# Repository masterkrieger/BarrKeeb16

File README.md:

# BarrKeeb16
 This is a 16 key macro keypad with a rotary encoder, OLED display and under-glow RGB. BarrKeeb16 is running KMK firmware on the Seeed XIAO RP2040.

# Parts
1. BarrKeeb16 custom PCB. [JLCPCB](https://jlcpcb.com/)
2. Seeed XIAO RP2040. [Digikey](https://www.digikey.com/en/products/detail/seeed-technology-co-ltd/102010428/14672129?s=N4IgTCBcDaIB4EsCGB7ABAJwA5gAwBZcQBdAXyA) ― [SeeedStudio](https://www.seeedstudio.com/XIAO-RP2040-v1-0-p-5026.html)
3. 16 × Diodes (SOD-123) [Digikey](https://www.digikey.ca/en/products/detail/smc-diode-solutions/1N4148W/6022450)
4. 16 × Cherry MX style switches. [Digikey](https://www.digikey.ca/en/products/detail/adafruit-industries-llc/4952/14113453) ― [Adafruit](https://www.adafruit.com/product/4952)
5. 16 × DSA style keycaps. [Digikey](https://www.digikey.ca/en/products/detail/adafruit-industries-llc/4998/14552195) ― [Adafruit](https://www.adafruit.com/product/4998)
6. 1 × Encoder (PEC11R). [Digikey](https://www.digikey.ca/en/products/detail/bourns-inc/PEC11R-4215F-S0024/4499665) ― [Adafruit](https://www.adafruit.com/product/377)
7. 4 × Neopixel 5050 (SK6812 or WS2812 _ 5mm × 5mm) [Digikey](https://www.digikey.ca/en/products/detail/adafruit-industries-llc/1655/5154679) ― [Adafruit](https://www.adafruit.com/product/1655)
8. 4 × 0.1 µF Capacitors 0603 (1608 Metric). [Digikey](https://www.digikey.ca/en/products/detail/samsung-electro-mechanics/CL10B104KB8NNNL/3894274)
9. 1 × Level shifter SOT-23-5. [Digikey](https://www.digikey.ca/en/products/detail/texas-instruments/74AHCT1G125DBVTG4/1687957)
10. 1 × PCF8574 IO Expander. [Digikey](https://www.digikey.ca/en/products/detail/nxp-usa-inc/PCF8574T-3-512/735690)
10. 1 × 10 kOhms Resistor 0805 (2012 Metric). [Digikey](https://www.digikey.ca/en/products/detail/stackpole-electronics-inc/RMCF0805JG10K0/1757769)
10. 1 × 4.7 kOhms Resistor 0805 (2012 Metric). [Digikey](https://www.digikey.ca/en/products/detail/stackpole-electronics-inc/RMCF0805JT4K70/1757774)
11. 5 × Screws (M2 × 2.5mm)
12. 4 × Rubber Bumper Feet. [Adafruit](https://www.adafruit.com/product/550)

# OLED Image
 If you want to replace the BarrKeeb16_screenlogo bitmap, create any black and white 128x64 pixel image and rename as 'BarrKeeb16_screenlogo.bmp' or 'BarrKeeb16_screenlogo_inverted.bmp' or modify the image filename in [display_logo.py](https://github.com/masterkrieger/BarrKeeb16/blob/main/Firmware/display_logo.py).

## TODO:
- Update STL models with new OLED position (v1.2).
- Update FIRMWARE with new RP2040 and IO Expander pinouts (v1.2).

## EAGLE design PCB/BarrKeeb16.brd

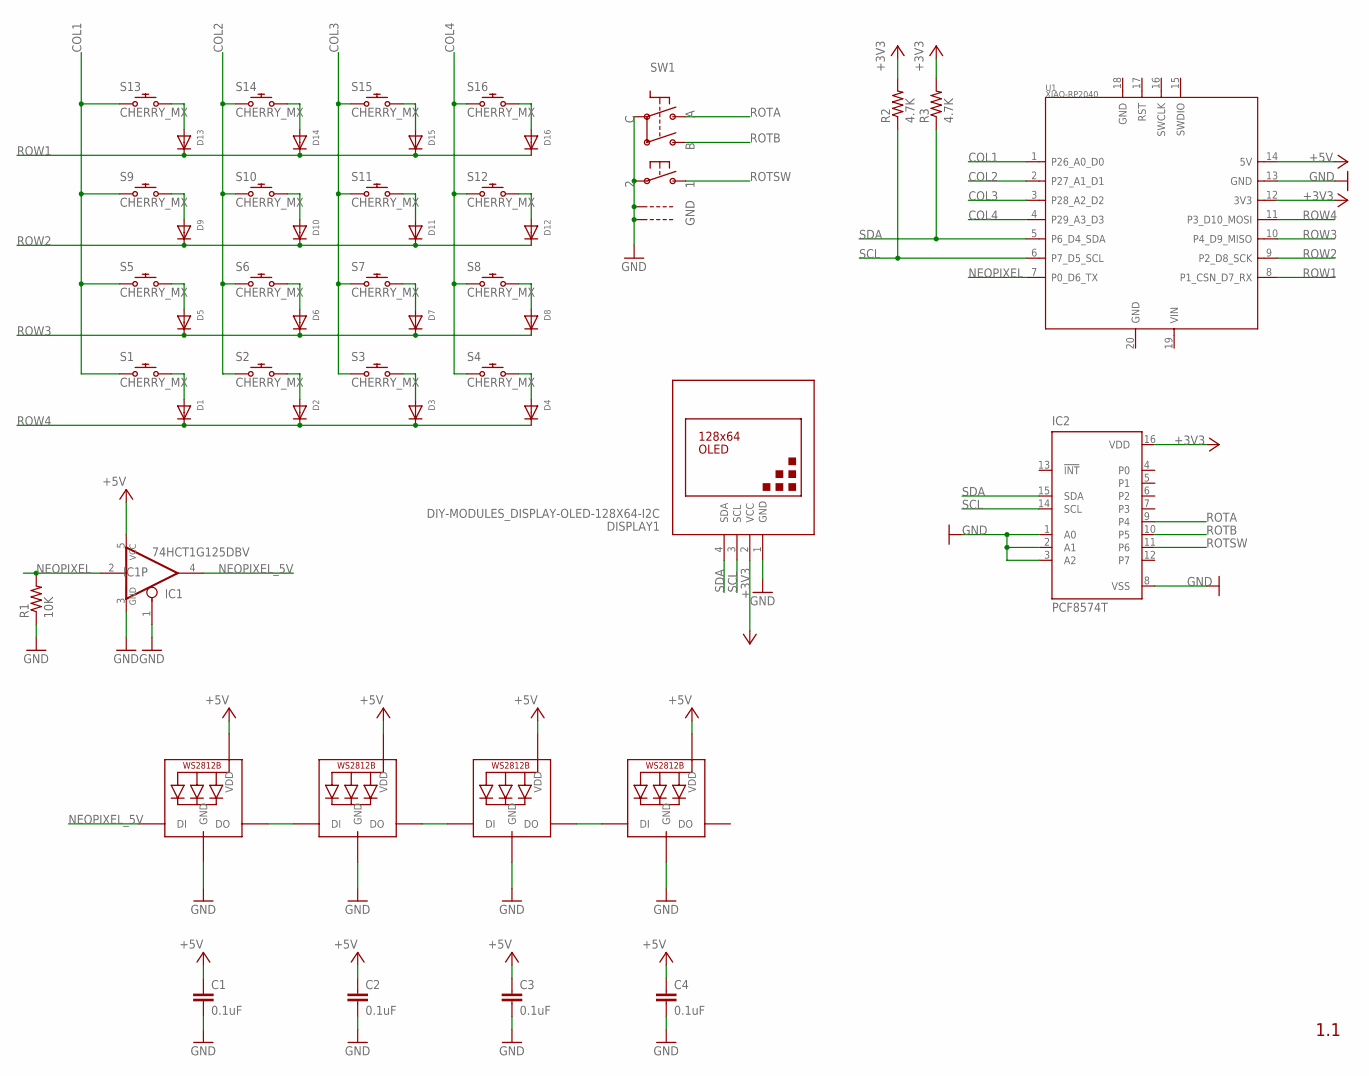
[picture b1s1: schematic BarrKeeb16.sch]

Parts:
C1, C2, C3, C4: 0.1uF; 0603
D1, D2, D3, D4, D5, D6, D7, D8, D9, D10, D11, D12, D13, D14, D15, D16: MICROBUILDER_DIODESOD-123; MICROBUILDER_SOD-123
DISPLAY1: DIY-MODULES_DISPLAY-OLED-128X64-I2C
IC1: 74HCT1G125DBV; SOT23-5
IC2: PCF8574T; SO16W
LED1, LED2, LED3, LED4: WS2812B5050; WS2812B
R1: 10K; R0805
R2, R3: 4.7K; R0805
S1, S2, S3, S4, S5, S6, S7, S8, S9, S10, S11, S12, S13, S14, S15, S16: CHERRY_MX
SW1: ADAFRUIT_ELECTROMECH_ENCODER_PLUS_SWITCH_BOURNS_P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; ADAFRUIT_ELECTROMECH_PEC11+SWITCH
U1: XIAO-RP2040; XIAO-SAMD21/RP2040-MODULE14P-2.54-21X17.8MM

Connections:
+3V3: DISPLAY1.2 (VCC), IC2.16 (VDD), R2.2, R3.2, U1.12 (3V3)
+5V: C1.1, C2.1, C3.1, C4.1, IC1.5 (VCC), LED1.1-VDD (VDD), LED2.1-VDD (VDD), LED3.1-VDD (VDD), LED4.1-VDD (VDD), U1.14 (5V)
COL1: S1.S1 (1), S5.S1 (1), S9.S1 (1), S13.S1 (1), U1.1 (P26_A0_D0)
COL2: S2.S1 (1), S6.S1 (1), S10.S1 (1), S14.S1 (1), U1.2 (P27_A1_D1)
COL3: S3.S1 (1), S7.S1 (1), S11.S1 (1), S15.S1 (1), U1.3 (P28_A2_D2)
COL4: S4.S1 (1), S8.S1 (1), S12.S1 (1), S16.S1 (1), U1.4 (P29_A3_D3)
GND: C1.2, C2.2, C3.2, C4.2, DISPLAY1.1 (GND), IC1.1 (OE), IC1.3 (GND), IC2.1 (A0), IC2.2 (A1), IC2.3 (A2), IC2.8 (VSS), LED1.3-GND (GND), LED2.3-GND (GND), LED3.3-GND (GND), LED4.3-GND (GND), R1.1, SW1.P$2, SW1.P$C, SW1.P$GND1, SW1.P$GND2, U1.13 (GND)
unnamed: D13.A, S13.S2 (2)
unnamed: D14.A, S14.S2 (2)
unnamed: LED1.2-DOUT (DO), LED2.4-DIN (DI)
unnamed: LED2.2-DOUT (DO), LED3.4-DIN (DI)
unnamed: LED3.2-DOUT (DO), LED4.4-DIN (DI)
unnamed: D15.A, S15.S2 (2)
unnamed: D16.A, S16.S2 (2)
unnamed: D9.A, S9.S2 (2)
unnamed: D10.A, S10.S2 (2)
unnamed: D11.A, S11.S2 (2)
unnamed: D12.A, S12.S2 (2)
unnamed: D5.A, S5.S2 (2)
unnamed: D6.A, S6.S2 (2)
unnamed: D7.A, S7.S2 (2)
unnamed: D8.A, S8.S2 (2)
unnamed: D1.A, S1.S2 (2)
unnamed: D2.A, S2.S2 (2)
unnamed: D3.A, S3.S2 (2)
unnamed: D4.A, S4.S2 (2)
NEOPIXEL: IC1.2 (I), R1.2, U1.7 (P0_D6_TX)
NEOPIXEL_5V: IC1.4 (O), LED1.4-DIN (DI)
ROTA: IC2.9 (P4), SW1.P$A
ROTB: IC2.10 (P5), SW1.P$B
ROTSW: IC2.11 (P6), SW1.P$1
ROW1: D13.C, D14.C, D15.C, D16.C, U1.8 (P1_CSN_D7_RX)
ROW2: D9.C, D10.C, D11.C, D12.C, U1.9 (P2_D8_SCK)
ROW3: D5.C, D6.C, D7.C, D8.C, U1.10 (P4_D9_MISO)
ROW4: D1.C, D2.C, D3.C, D4.C, U1.11 (P3_D10_MOSI)
SCL: DISPLAY1.3 (SCL), IC2.14 (SCL), R2.1, U1.6 (P7_D5_SCL)
SDA: DISPLAY1.4 (SDA), IC2.15 (SDA), R3.1, U1.5 (P6_D4_SDA)

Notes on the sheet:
1.1

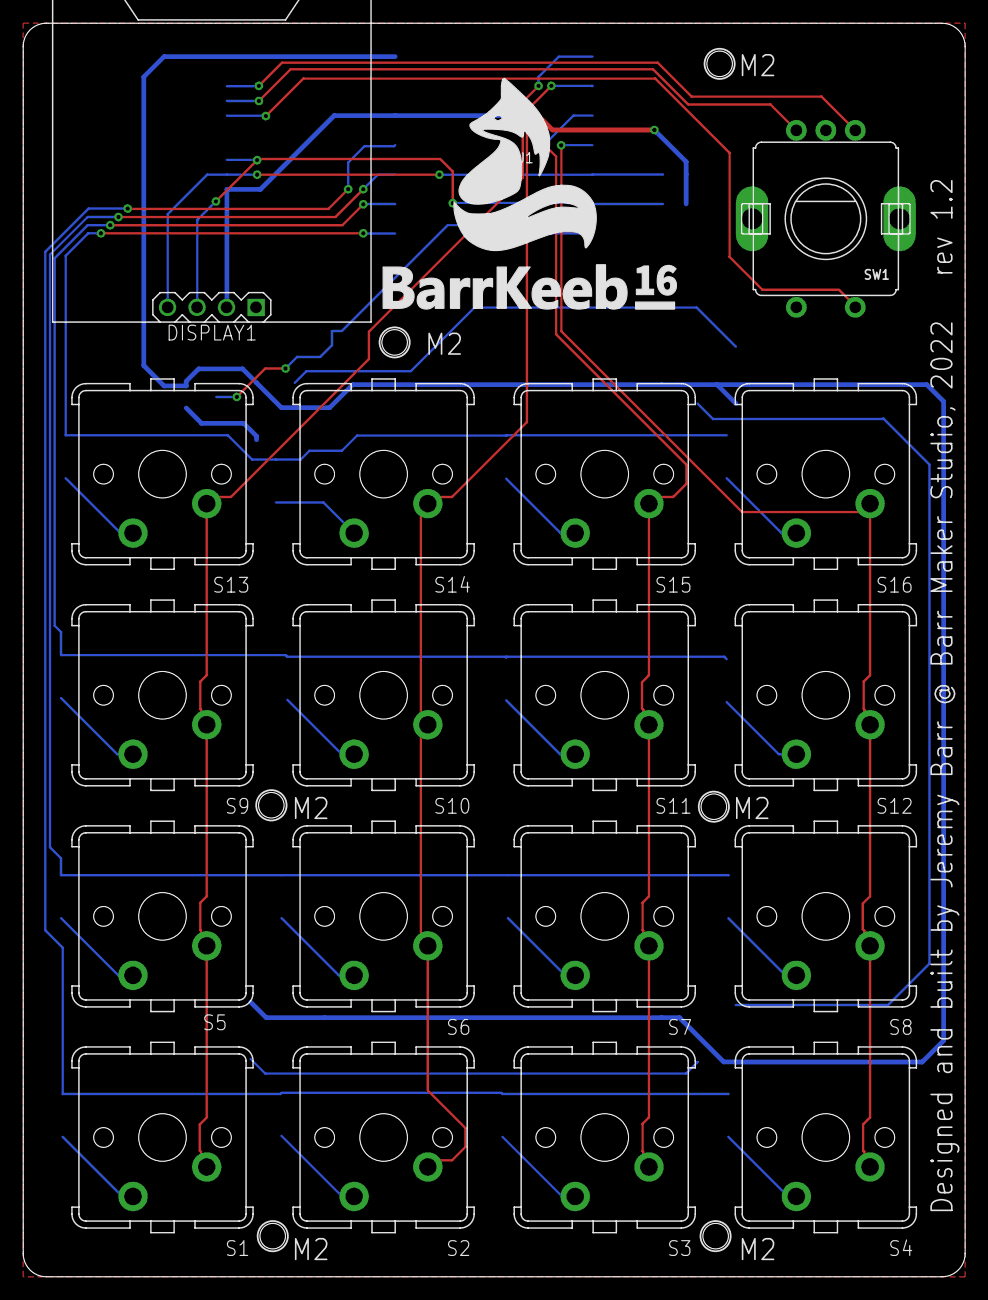
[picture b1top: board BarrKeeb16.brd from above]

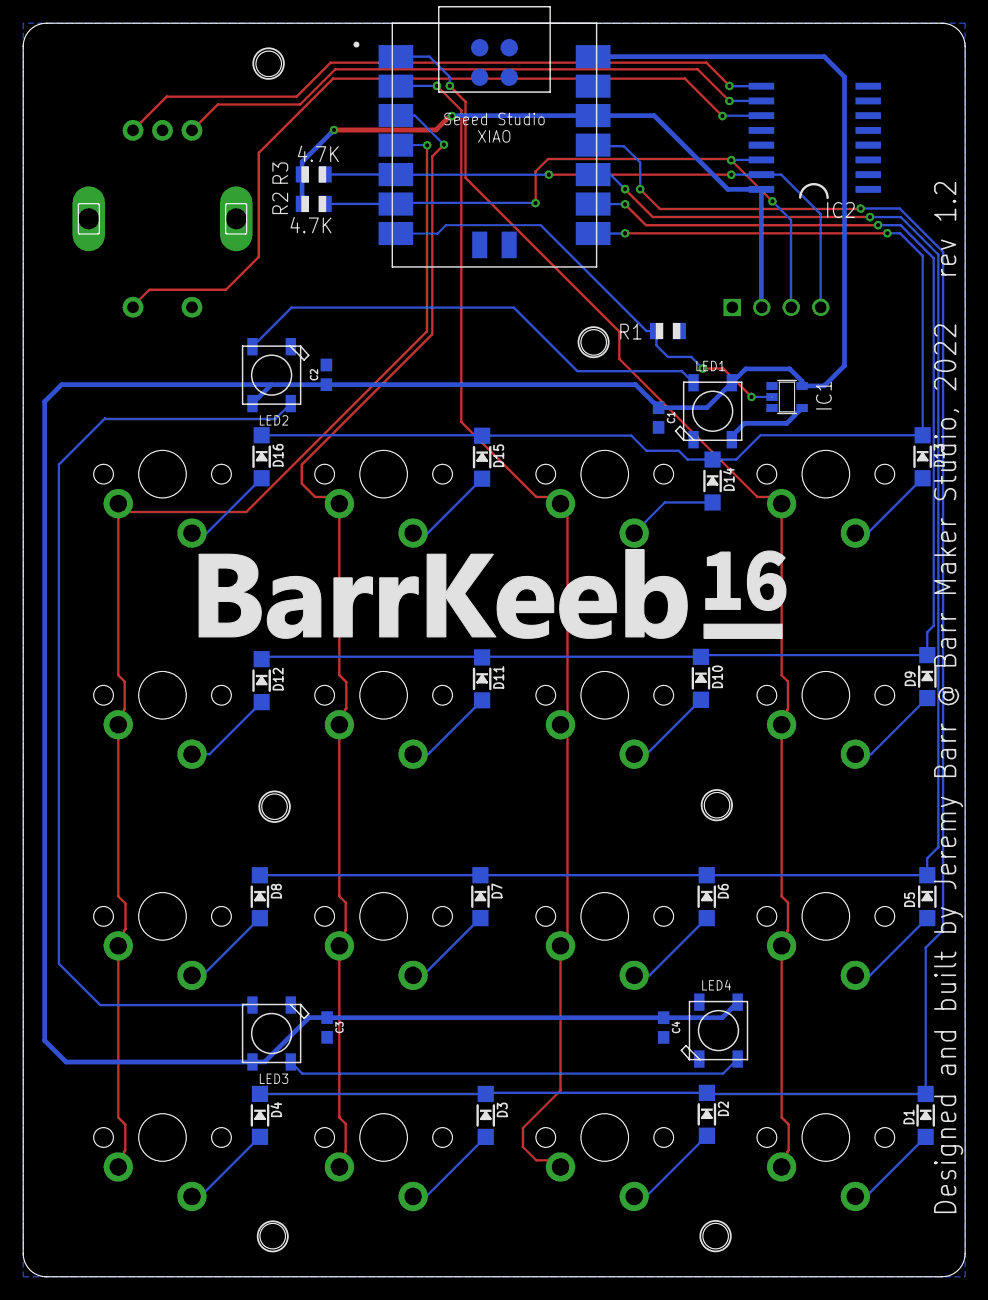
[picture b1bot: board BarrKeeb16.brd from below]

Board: 2 copper layers, 81.2 x 108.0 mm, 50 parts (31 on the bottom side), 37 nets.

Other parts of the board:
U$1: BARRKEEP16-LOGO
U$2: BARRKEEB-16

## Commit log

2023-01-28 Init Upload
    Working code v1.0
2023-01-30 Update README.md
    Added parts list and updated description.
2023-01-30 v1.2 - swapped keys and encoder pinout
    - Moved keyswitches to the RP2040
    - Moved encoder to PCF8574 IO Expander
    - Updated EAGLE schematic and board to incorporate new routing layout.
2023-01-30 Remove extra files
2023-03-07 Update PCB and Case
    PCB:
    - Moved OLED up so it doesn't interfere with keyswitches.
    - Moved encoder pinout to the IO Expander.
    - Moved Keyswitches pinouts to the RP2040.
    CASE:
    - Added a 6deg incline to bottom case
2026-05-22 Updating to version 1.3
    - Updated to v1.3 to update KMK and add custom libraries for the IO extender and rgb.py (KMK) to work on this custom board.
    - Added feature: Display current layer and layer labels and RGB.py updated to run on this board.
    - This is for PCB v1.1 (pdf).
    - The PCB v1.2 is for a different version of software thats still in-work.

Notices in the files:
parts and their libraries:
SparkFun-Capacitors: Licensing: Creative Commons ShareAlike 4.0 International - https://creativecommons.org/licenses/by-sa/4.0
